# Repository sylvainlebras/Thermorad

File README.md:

# Thermorad
Intuitive EMC tool with visual feedback

This tool is meant to be used for EMC investigation and EMC teaching, it provides a simple and quick feedback through an 8 LED indicator.

Possible use includes : 
- Locating near H-field emission sources 
- Locating near E-field emission sources (requires E Field antenna)
- Demonstrating polarisation of emitters-receivers
- Locating wifi and 4G/5G antennas on a phone
- Evaluation of perturbations carried by a cable (requires ferrite clamp)

Coming next
- Version D with Geiger like sound output
- E-Field antenna
- Small diameter H Field antenna

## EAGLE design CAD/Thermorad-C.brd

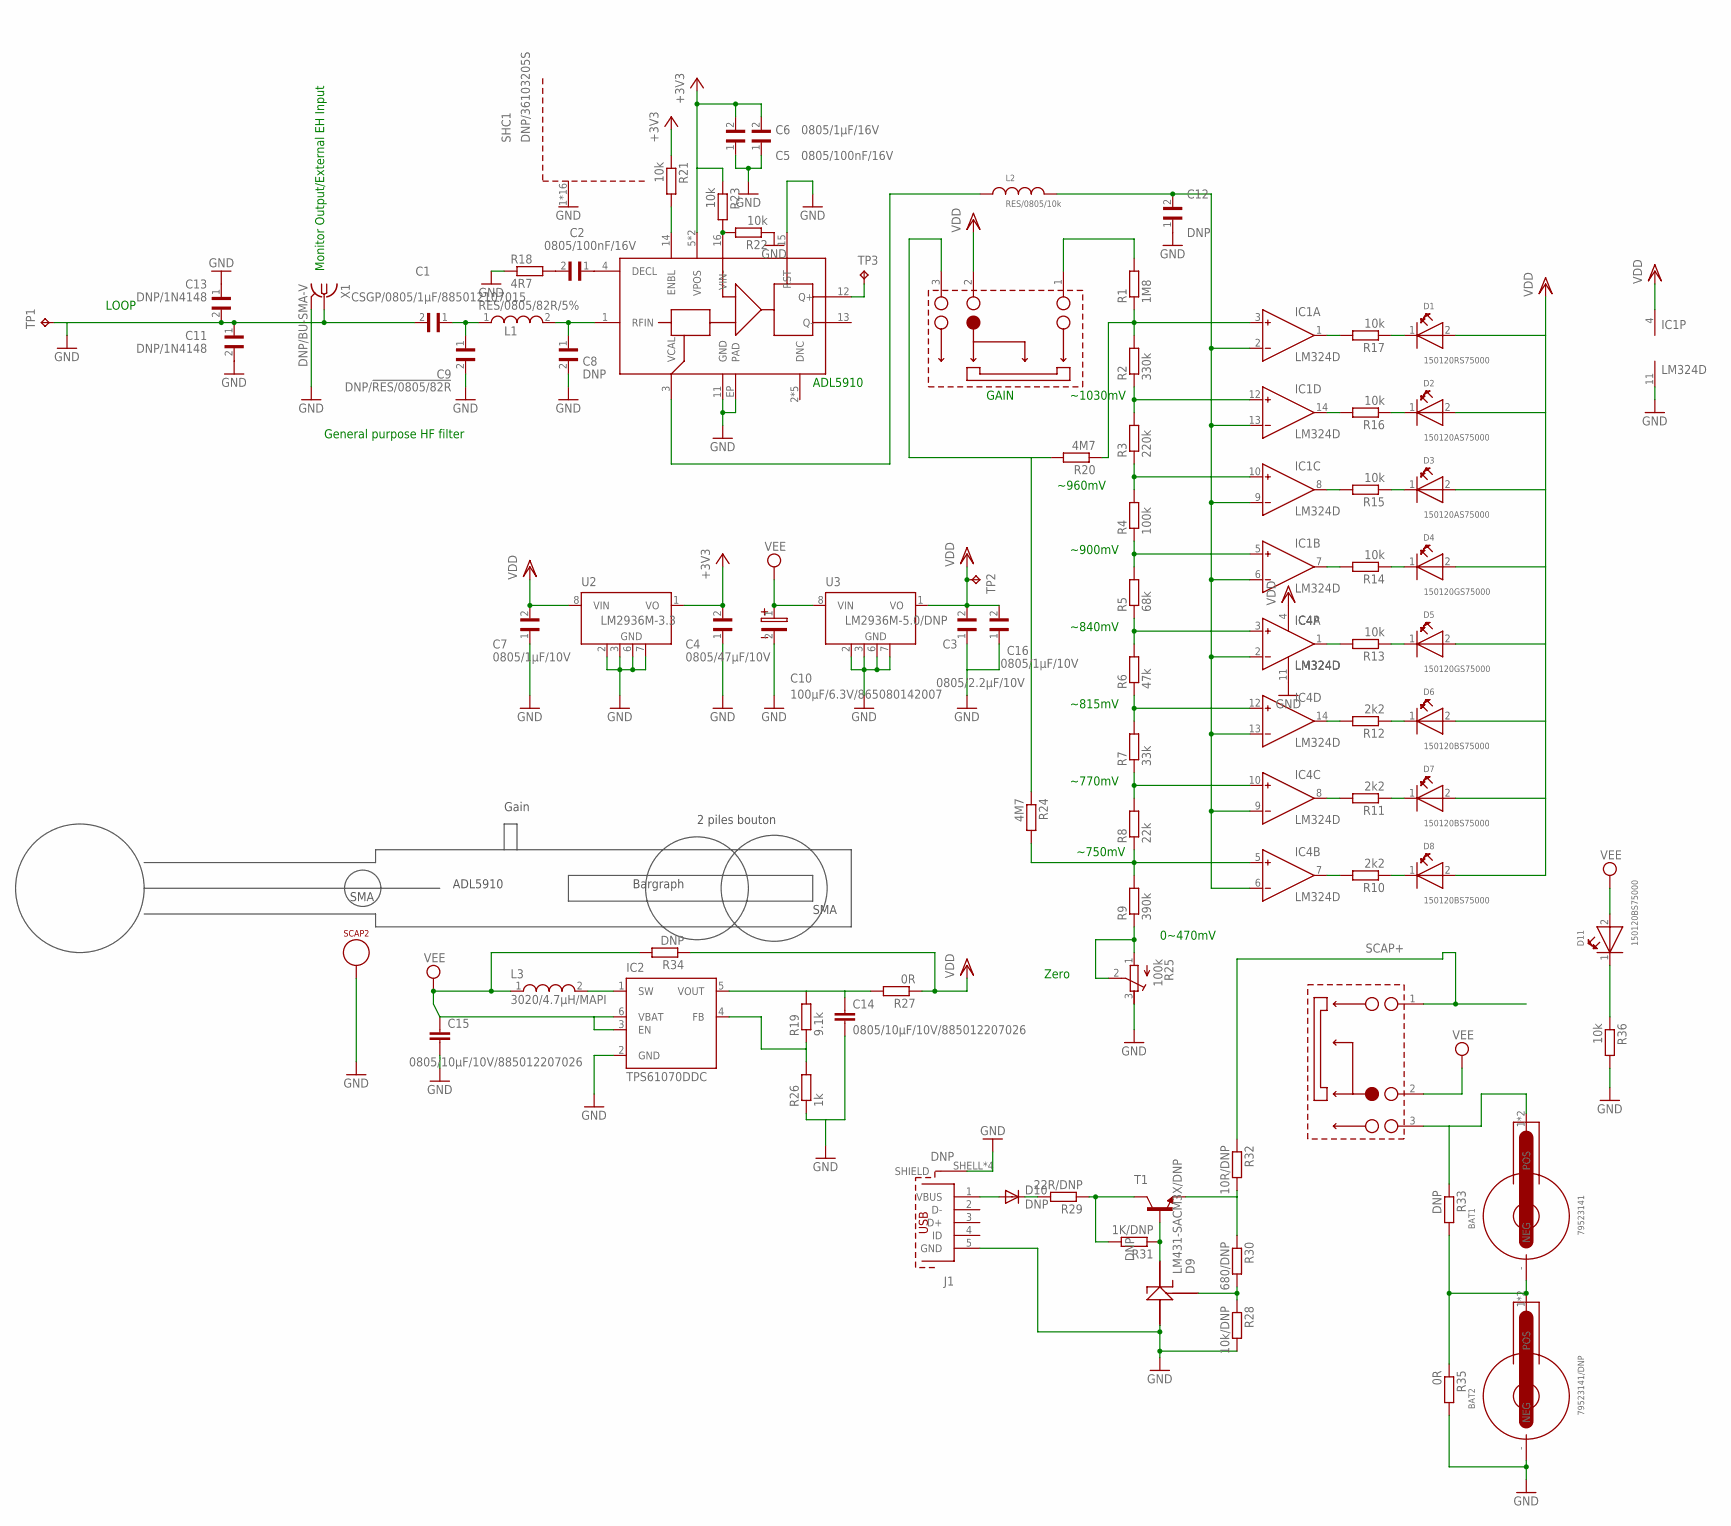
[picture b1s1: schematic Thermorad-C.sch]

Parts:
BAT1: 79523141
BAT2: 79523141/DNP; 79523141
C1: CSGP/0805/1µF/885012107015; WCAP-CSGP_0805_REFLOW
C2, C5: 0805/100nF/16V; WCAP-CSGP_0805_REFLOW
C3: 0805/2.2µF/10V; WCAP-CSGP_0805_REFLOW
C4: 0805/47µF/10V; WCAP-CSGP_0805_REFLOW
C6: 0805/1µF/16V; WCAP-CSGP_0805_REFLOW
C7, C16: 0805/1µF/10V; WCAP-CSGP_0805_REFLOW
C8, C12: DNP; WCAP-CSGP_0805_REFLOW
C9: DNP/!RES/0805/82R; WCAP-CSGP_0805_REFLOW
C10: 100µF/6.3V/865080142007; 3X1.6X1.4(BXCXA)
C11, C13: DNP/1N4148; WCAP-CSGP_0805_REFLOW
C14, C15: 0805/10µF/10V/885012207026; C0805
D1: 150120RS75000; 1206
D2, D3: 150120AS75000; 1206
D4, D5: 150120GS75000; 1206
D6, D7, D8, D11: 150120BS75000; 1206
D9: LM431-SACM3X/DNP; SOT23
D10: DNP; SOD123
IC1: LM324D; SO14; MPN AD8644ARZ
IC2: TPS61070DDC; TSOT23-6_DDC
IC4: LM324D; SO14
J1: DNP; 629105150521
L1: RES/0805/82R/5%; WE-KI_0805A
L2: RES/0805/10k; WE-CBF_0805(W=3.0)
L3: 3020/4.7µH/MAPI; WE-MAPI_3015/3020
R1: 1M8; M0805
R2: 330k; M0805
R3: 220k; M0805
R4: 100k; M0805
R5: 68k; M0805
R6: 47k; M0805
R7: 33k; M0805
R8: 22k; M0805
R9: 390k; M0805
R10, R11, R12: 2k2; M0805
R13, R14, R15, R16, R17, R21, R22, R23, R36: 10k; M0805
R18: 4R7; M0805
R19: 9.1k; R0805
R20, R24: 4M7; M0805
R25: 100k; RTRIM3224X
R26: 1k; R0805
R27, R35: 0R; R0805
R28: 10k/DNP; R0805
R29: 22R/DNP; R0805
R30: 680/DNP; R0805
R31: 1K/DNP; R0805
R32: 10R/DNP; R0805
R33, R34: DNP; R0805
SCAP2: TESTPOINT-GROS
SHC1: DNP/36103205S; WE-SHC_36103205S
SW1, SW2: 450404015514
T1: DNP; SOT89-BCE
TP1, TP2: TPB2,54; B2,54
TP3: TPB1,27; B1,27
U1: ADL5910; LFCSP-16
U2: LM2936M-3.3; SO08
U3: LM2936M-5.0/DNP; SO08
X1: DNP/BU-SMA-V; BU-SMA-V

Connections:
+3V3: C4.2, C5.2, C6.2, R21.1, R23.1, U1.5 (VPOS), U1.7 (VPOS), U2.1 (VO)
GND: BAT2.- (NEG), C1.2, C3.1, C4.1, C5.1, C6.1, C7.1, C8.2, C9.2, C10.2, C11.1, C11.2, C12.1, C13.1, C13.2, C14.2, C15.2, C16.1, D9.3 (A), IC1.11 (V-), IC2.2 (GND), IC4.11 (V-), J1.5 (GND), J1.SHELL (SHIELD), J1.SHELL1 (SHIELD), J1.SHELL2 (SHIELD), J1.SHELL3 (SHIELD), R18.1, R22.1, R25.3 (A), R26.1, R28.2, R35.2, R36.2, SCAP2.1, SHC1.1, SHC1.2, SHC1.3, SHC1.4, SHC1.5, SHC1.6, SHC1.7, SHC1.8, SHC1.9, SHC1.10, SHC1.11, SHC1.12, SHC1.13, SHC1.14, SHC1.15, SHC1.16, TP1.TP, U1.11 (GND), U1.15 (RST), U1.EP (PAD), U2.2 (GND), U2.3 (GND), U2.6 (GND), U2.7 (GND), U3.2 (GND), U3.3 (GND), U3.6 (GND), U3.7 (GND), X1.1, X1.2 (GND), X1.3 (GND), X1.4 (GND), X1.5 (GND)
unnamed: IC2.1 (SW), L3.2
unnamed: IC4.10 (IN+), R7.1, R8.2
unnamed: IC4.12 (IN+), R6.1, R7.2
unnamed: IC4.3 (IN+), R5.1, R6.2
unnamed: IC1.5 (IN+), R4.1, R5.2
unnamed: IC1.10 (IN+), R3.1, R4.2
unnamed: IC1.12 (IN+), R2.1, R3.2
unnamed: IC1.3 (IN+), R1.1, R2.2, R20.1
unnamed: C1.1, C9.1, L1.1
unnamed: IC4.14 (OUT), R12.2
unnamed: C8.1, L1.2, U1.1 (RFIN)
unnamed: IC1.1 (OUT), R17.2
unnamed: D1.1 (K), R17.1
unnamed: IC1.14 (OUT), R16.2
unnamed: D6.1 (K), R12.1
unnamed: IC4.8 (OUT), R11.2
unnamed: D7.1 (K), R11.1
unnamed: D2.1 (K), R16.1
unnamed: IC1.8 (OUT), R15.2
unnamed: IC4.7 (OUT), R10.2
unnamed: D8.1 (K), R10.1
unnamed: D3.1 (K), R15.1
unnamed: IC1.7 (OUT), R14.2
unnamed: D4.1 (K), R14.1
unnamed: IC4.1 (OUT), R13.2
unnamed: D5.1 (K), R13.1
unnamed: BAT1.1 (POS), BAT1.2 (POS), R33.1, SW2.3
unnamed: BAT1.- (NEG), BAT2.1 (POS), BAT2.2 (POS), R33.2, R35.1
unnamed: R1.2, SW1.1
unnamed: C2.1, U1.4 (DECL)
unnamed: C2.2, R18.2
unnamed: C12.2, IC1.2 (IN-), IC1.6 (IN-), IC1.9 (IN-), IC1.13 (IN-), IC4.2 (IN-), IC4.6 (IN-), IC4.9 (IN-), IC4.13 (IN-), L2.2
unnamed: R9.1, R25.1 (E), R25.2 (S)
unnamed: L2.1, U1.3 (VCAL)
unnamed: R21.2, U1.14 (ENBL)
unnamed: R20.2, R24.1, SW1.3
unnamed: R22.2, R23.2, U1.16 (VIN-)
unnamed: R30.1, R32.2, T1.E
unnamed: TP3.TP, U1.12 (Q+)
unnamed: IC4.5 (IN+), R8.1, R9.2, R24.2
unnamed: IC2.4 (FB), R19.1, R26.2
unnamed: C14.1, IC2.5 (VOUT), R19.2, R27.2
unnamed: D11.1 (K), R36.1
unnamed: D10.A, J1.1 (VBUS)
unnamed: D10.C, R29.2
unnamed: R29.1, R31.2, T1.C
unnamed: D9.1 (K), R31.1, T1.B
unnamed: D9.2 (REF), R28.1, R30.2
SCAP+: R32.1, SW2.1
VDD: C3.2, C7.2, C16.2, D1.2 (A), D2.2 (A), D3.2 (A), D4.2 (A), D5.2 (A), D6.2 (A), D7.2 (A), D8.2 (A), IC1.4 (V+), IC4.4 (V+), R27.1, R34.1, SW1.2, TP2.TP, U2.8 (VIN), U3.1 (VO)
VEE: C10.1, C15.1, D11.2 (A), IC2.3 (EN), IC2.6 (VBAT), L3.1, R34.2, SW2.2, U3.8 (VIN)

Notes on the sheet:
ADL5910
SMA
2 piles bouton
Bargraph
Gain
~750mV
0~470mV
Zero
GAIN
~770mV
~815mV
~840mV
~900mV
~960mV
~1030mV
LOOP
General purpose HF filter
Monitor Output/External EH Input

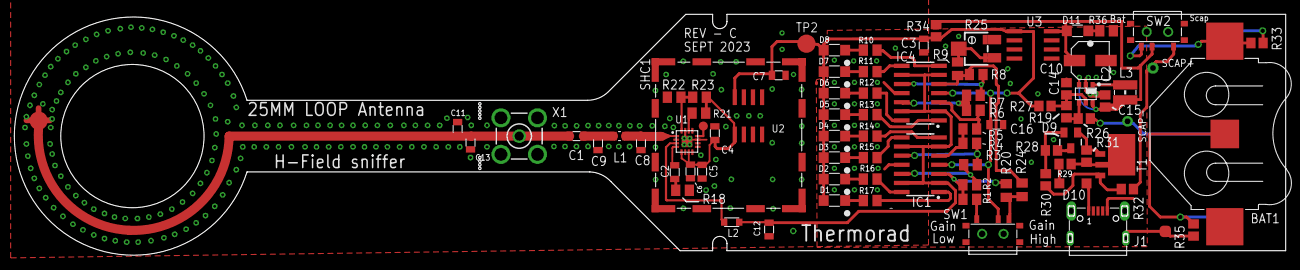
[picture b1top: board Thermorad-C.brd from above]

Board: 2 copper layers, 177.4 x 33.5 mm, 84 parts (1 on the bottom side), 53 nets.

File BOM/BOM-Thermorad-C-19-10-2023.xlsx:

Parts | Qty | Value | Device | Package | Description | Manufacturer
C2, C5 | 2 | 0805/100nF/16V | 885012207045 | WCAP-CSGP_0805_REFLOW | WCAP-CSGP Ceramic Capacitors | Wurth-Elektronik / Generic
C14, C15 | 2 | 0805/10µF/10V | 885012207026 | C0805 | CAPACITOR, European symbol | Wurth-Elektronik / Generic
C7, C16 | 2 | 0805/1µF/10V | 885012207051 | WCAP-CSGP_0805_REFLOW | WCAP-CSGP Ceramic Capacitors | Wurth-Elektronik / Generic
C6 | 1 | 0805/1µF/16V | 885012207051 | WCAP-CSGP_0805_REFLOW | WCAP-CSGP Ceramic Capacitors | Wurth-Elektronik / Generic
C3 | 1 | 0805/2.2µF/10V | 885012207024 | WCAP-CSGP_0805_REFLOW | WCAP-CSGP Ceramic Capacitors | Wurth-Elektronik / Generic
C4 | 1 | 0805/22µF/10V | 885012107011 | WCAP-CSGP_0805_REFLOW | WCAP-CSGP Ceramic Capacitors | Wurth-Elektronik / Generic
R27, R35 | 2 | 0R | R-EU_R0805 | R0805 | RESISTOR, European symbol | Generic
R4 | 1 | 100k | R-EU_M0805 | M0805 | RESISTOR, European symbol | Generic
R25 | 1 | 100k/TC33X-2-104G | R-TRIMM3224X | RTRIM3224X | Trimm resistor | Bourns / Generic
C10 | 1 | 100µF/6.3V/865080142007 | WCAP-ASLI_5X5.5(DXL) | 3X1.6X1.4(BXCXA) | WCAP-ASLI Aluminum Electrolytic Capacitors | Wurth-Elektronik
R32 | 1 | 10R/DNP | R-EU_R0805 | R0805 | RESISTOR, European symbol
R13, R14, R15, R16, R17, R21, R22, R23, R36 | 9 | 10k | R-EU_M0805 | M0805 | RESISTOR, European symbol | Generic
R28 | 1 | 10k/DNP | R-EU_R0805 | R0805 | RESISTOR, European symbol
D2, D3 | 2 | 150120AS75000 | WL-SMCW-150120GS75000-G | 1206 | SMD mono-color Chip LED | Wurth-Elektronik
D6, D7, D8, D11 | 4 | 150120BS75000 | WL-SMCW-150120GS75000-G | 1206 | SMD mono-color Chip LED | Wurth-Elektronik
D4, D5 | 2 | 150120GS75000 | WL-SMCW-150120GS75000-G | 1206 | SMD mono-color Chip LED | Wurth-Elektronik
D1 | 1 | 150120RS75000 | WL-SMCW-150120GS75000-G | 1206 | SMD mono-color Chip LED | Wurth-Elektronik
R31 | 1 | 1K/DNP | R-EU_R0805 | R0805 | RESISTOR, European symbol
R1 | 1 | 1M8 | R-EU_M0805 | M0805 | RESISTOR, European symbol | Generic
R26 | 1 | 1k | R-EU_R0805 | R0805 | RESISTOR, European symbol | Generic
R3 | 1 | 220k | R-EU_M0805 | M0805 | RESISTOR, European symbol | Generic
R29 | 1 | 22R/DNP | R-EU_R0805 | R0805 | RESISTOR, European symbol
R8 | 1 | 22k | R-EU_M0805 | M0805 | RESISTOR, European symbol | Generic
R10, R11, R12 | 3 | 2k2 | R-EU_M0805 | M0805 | RESISTOR, European symbol | Generic
L3 | 1 | 74438336047 | WE-MAPI_3015/3020 | WE-MAPI_3015/3020 | SMD Metal Alloy Power Inductor | Wurth-Elektronik
R2 | 1 | 330k | R-EU_M0805 | M0805 | RESISTOR, European symbol | Generic
R7 | 1 | 33k | R-EU_M0805 | M0805 | RESISTOR, European symbol | Generic
R9 | 1 | 390k | R-EU_M0805 | M0805 | RESISTOR, European symbol | Generic
SW1, SW2 | 2 | 450404015514 | 450404015514 | 450404015514 | WS-SLSU | Wurth-Elektronik
R6 | 1 | 47k | R-EU_M0805 | M0805 | RESISTOR, European symbol | Generic
R20, R24 | 2 | 4M7 | R-EU_M0805 | M0805 | RESISTOR, European symbol | Generic
R18 | 1 | 4R7 | R-EU_M0805 | M0805 | RESISTOR, European symbol | Generic
R30 | 1 | 680/DNP | R-EU_R0805 | R0805 | RESISTOR, European symbol
R5 | 1 | 68k | R-EU_M0805 | M0805 | RESISTOR, European symbol | Generic
BAT1 | 1 | 79523141 | WA-BCMC_SMT_79523141 | 79523141 | Battery Holder WA-BCMC | Wurth-Elektronik
BAT2 | 1 | 79523141/DNP | WA-BCMC_SMT_79523141 | 79523141 | Battery Holder WA-BCMC
R19 | 1 | 9.1k | R-EU_R0805 | R0805 | RESISTOR, European symbol | Generic
U1 | 1 | ADL5910 | ADL5910 | LFCSP-16 |  | Analog Devices
C1 | 1 | 0805/1µF | 885012207051 | WCAP-CSGP_0805_REFLOW | WCAP-CSGP Ceramic Capacitors | Wurth-Elektronik / Generic
J1 | 1 | DNP | 629105150521 | 629105150521 | WR-COM_USB_Micro Type B_Horizontal_SMT ;
T1 | 1 | DNP | BF622-NPN-SOT89-BCE | SOT89-BCE | NPN Transistror
D10 | 1 | DNP | DIODE-SOD123 | SOD123 | DIODE
R33, R34 | 2 | DNP | R-EU_R0805 | R0805 | RESISTOR, European symbol
C8, C12 | 2 | DNP | WCAP-CSGP_0805-REFLOW | WCAP-CSGP_0805_REFLOW | WCAP-CSGP Ceramic Capacitors
C9 | 1 | DNP/!RES/0805/82R | WCAP-CSGP_0805-REFLOW | WCAP-CSGP_0805_REFLOW | WCAP-CSGP Ceramic Capacitors
C11, C13 | 2 | DNP/1N4148 | WCAP-CSGP_0805-REFLOW | WCAP-CSGP_0805_REFLOW | WCAP-CSGP Ceramic Capacitors
SHC1 | 1 | DNP/36103205S | WE-SHC_36103205S | WE-SHC_36103205S | Shielding Cabinet
X1 | 1 | DNP/BU-SMA-V | BU-SMA-V | BU-SMA-V | FEMALE SMA CONNECTOR
U2 | 1 | LM2936M-3.3 | LM2936M-3.3 | SO08 | Ultra-Low Quiescent Current LDO Voltage Regulator | Texas Instruments
U3 | 1 | LM2936M-5.0/DNP | LM2936M-5.0 | SO08 | Ultra-Low Quiescent Current LDO Voltage Regulator
IC1, IC4 | 2 | LM324D | Many more like AD8644R | SO14 | Single and Quad 18 V Operational Amplifiers | Generic
D9 | 1 | LM431-SACM3X/DNP | LM431-SACM3X | SOT23
L2 | 1 | RES/0805/10k |  | 805 | WE-CBF SMD EMI Suppression Ferrite Bead | Generic
L1 | 1 | RES/0805/82R/5% |  | 805 | SMD Wire Wound Ceramic Inductor | Generic
SCAP2 | 1 | TESTPOINT-GROS | TESTPOINT-GROS | TESTPOINT-GROS
TP3 | 1 | TPB1,27 | TPB1,27 | B1,27 | Test pad
TP1, TP2 | 2 | TPB2,54 | TPB2,54 | B2,54 | Test pad
IC2 | 1 | TPS61070DDC | TPS61070DDC | TSOT23-6_DDC | 90% EFFICIENT SYNCHRONOUS BOOST CONVERTER WITH 600-mA SWITCH | Texas Instruments

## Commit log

2019-03-21 Create empty
2019-03-21 Create Notice
2019-03-21 Eagle source files
2023-10-18 Update C
2023-10-18 Update C - Cheaper Potentiometer implanted
2023-10-18 Better Image
2023-10-19 Update BOM with partnumber and DNP

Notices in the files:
parts and their libraries:
Wurth_Elektronik_Optoelectronics_rev15b: Copyright: Würth Elektronik
